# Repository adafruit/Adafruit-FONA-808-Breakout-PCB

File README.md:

## Adafruit FONA 808 Breakout PCB
<a href="http://www.adafruit.com/products/2542"><br/>
Click here to purchase one from the Adafruit shop</a>

Cellular + GPS tracking, all in one? Oh yes! Introducing Adafruit FONA 808 MiniGSM + GPS, an all-in-one cellular phone module with that lets you add location-tracking, voice, text, SMS and data to your project in an adorable little package. (It does not contain a drum machine, tho)

This module measures only 1.75"x1.6" but packs a surprising amount of technology into it's little frame. At the heart is a powerful GSM cellular module (we use the latest SIM808) with integrated GPS. This module can do just about everything.

PCB files for the Adafruit FONA 808 Breakout. The format is EagleCAD schematic and board layout
 https://www.adafruit.com/products/2542 

### License

Adafruit invests time and resources providing this open source design, please support Adafruit and open-source hardware by purchasing products from [Adafruit](https://www.adafruit.com)!

All text above must be included in any redistribution

Designed by Limor Fried/Ladyada for Adafruit Industries.
Creative Commons Attribution/Share-Alike, all text above must be included in any redistribution. 
See license.txt for additional information.

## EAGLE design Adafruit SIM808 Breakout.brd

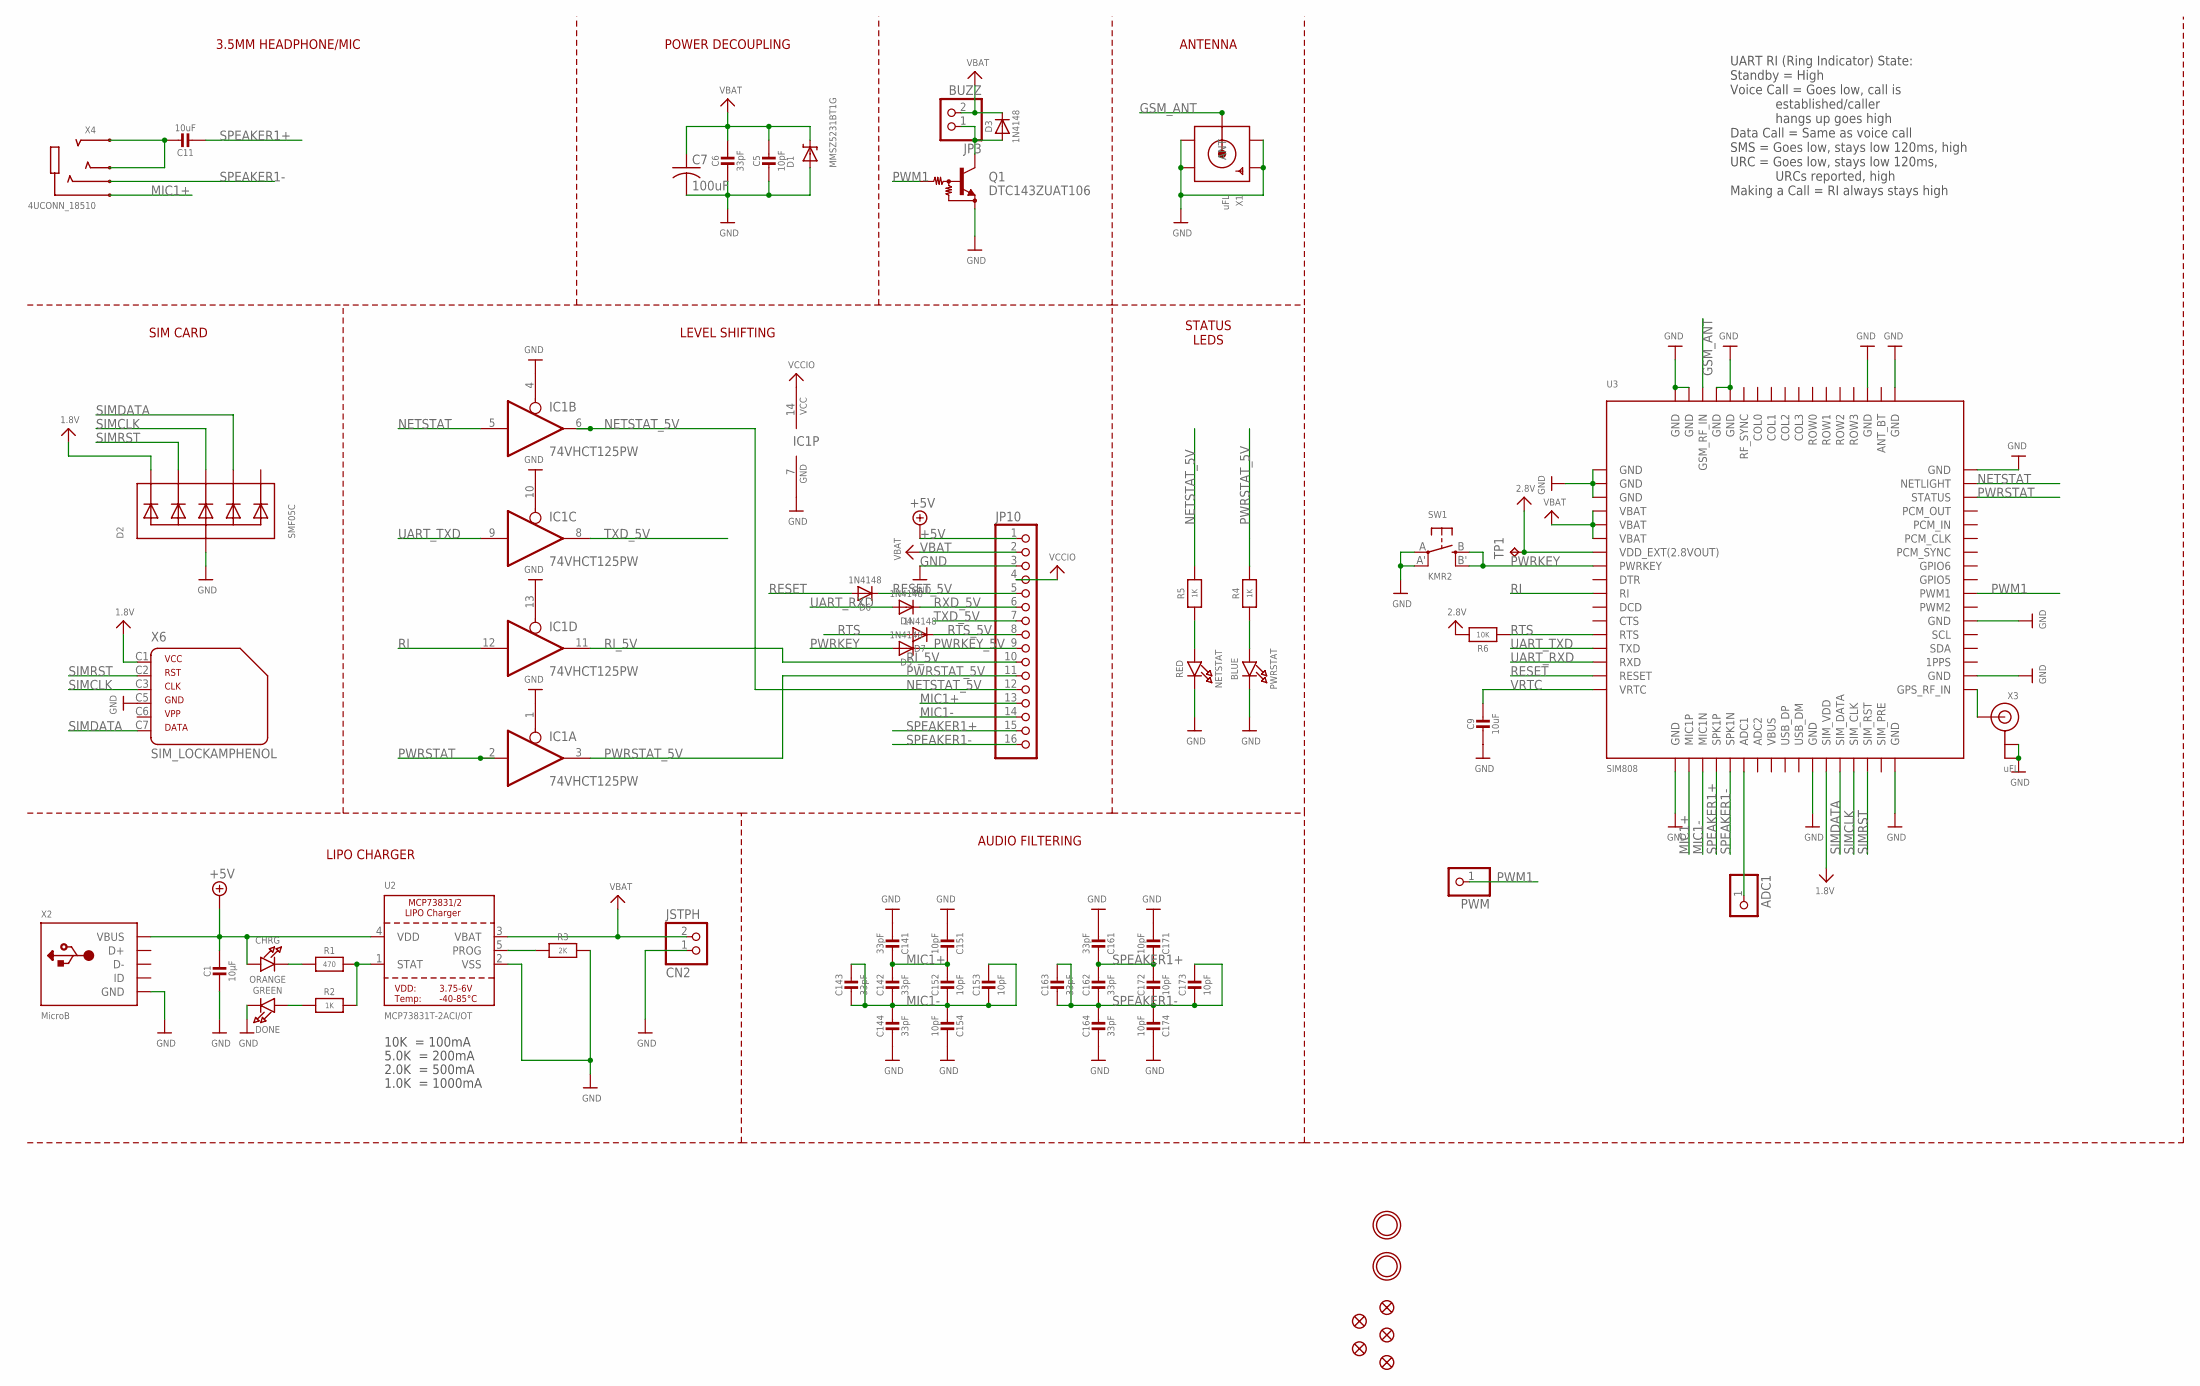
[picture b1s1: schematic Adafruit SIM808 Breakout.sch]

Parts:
ADC1: PINHD-1X1CB; 1X01-CLEANBIG
C1: 10µF; 0805-NO
C5: 10pF; 0805-NO
C6: 33pF; 0805-NO
C7: 100uF; C1210
C9, C11: 10uF; 0805-NO
C14, C16: 33pF; RESPACK_4X0603
C15, C17: 10pF; RESPACK_4X0603
CHRG: ORANGE; CHIPLED_0805_NOOUTLINE
CN2: JSTPH; JSTPH2
D1: MMSZ5231BT1G; SOD-123
D2: SMF05C; SOT363
D3, D4, D5, D6, D7: 1N4148; SOD-323
DONE: GREEN; CHIPLED_0805_NOOUTLINE
FID1, FID2, FID3, FID4, FID5: FIDUCIAL""; FIDUCIAL_1MM
IC1: 74VHCT125PW; TSSOP14
JP3: BUZZ; 1X02_ROUND
JP10: HEADER-1X16ROUND; 1X16_ROUND
NETSTAT: RED; CHIPLED_0805_NOOUTLINE
PWM: PINHD-1X1CB; 1X01-CLEANBIG
PWRSTAT: BLUE; CHIPLED_0805_NOOUTLINE
Q1: DTC143ZUAT106; SC59-BEC
R1: 470; 0805-NO
R2, R4, R5: 1K; 0805-NO
R3: 2K; 0805-NO
R6: 10K; 0805-NO
SW1: KMR2; BTN_KMR2_4.6X2.8
TP1: TPTP11R; TP11R
U2: MCP73831T-2ACI/OT; SOT23-5
U3: SIM808; SIM900_SMT
U$33, U$34: MOUNTINGHOLE2.5; MOUNTINGHOLE_2.5_PLATED
X1: uFL; SMA_EDGELAUNCH_UFL
X2: MicroB; 4UCONN_20329
X3: uFL; U.FL
X4: 4UCONN_18510
X6: SIM_LOCKAMPHENOL; C707_10M006_512_2

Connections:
1.8V: D2.1 (C1), U3.P$29 (SIM_VDD), X6.C1 (1)
2.8V: R6.2, TP1.TP, U3.P$7 (VDD_EXT(2.8VOUT))
+5V: C1.1, CHRG.A, JP10.1, U2.4 (VDD), X2.VBUS
GND: C1.2, C5.2, C6.2, C7.2, C9.2, C14.5 (2), C14.8 (2), C15.4 (1), C15.8 (2), C16.5 (2), C16.8 (2), C17.4 (1), C17.8 (2), CN2.1, D1.A, D2.2 (A), DONE.C, IC1.1 (OE), IC1.4 (OE), IC1.7 (GND), IC1.10 (OE), IC1.13 (OE), JP10.3, NETSTAT.C, PWRSTAT.C, Q1.E, R3.2, SW1.A, SW1.A' (P1), U2.2 (VSS), U3.P$1 (GND), U3.P$2 (GND), U3.P$3 (GND), U3.P$18 (GND), U3.P$28 (GND), U3.P$34 (GND), U3.P$36 (GND), U3.P$40 (GND), U3.P$51 (GND), U3.P$52 (GND), U3.P$54 (GND), U3.P$64 (GND), U3.P$65 (GND), U3.P$67 (GND), U3.P$68 (GND), X1.GND@1 (GND1), X1.GND@2 (GND2), X1.GND@3 (GND3), X1.GND@4 (GND4), X2.BASE@1 (GND), X2.BASE@2 (GND), X2.GND, X2.SPRT@1 (GND), X2.SPRT@2 (GND), X2.SPRT@3 (GND), X2.SPRT@4 (GND), X3.1 (GND), X3.2 (GND), X6.C5 (4)
GSM_ANT: U3.P$66 (GSM_RF_IN), X1.P (ANT)
HP+: C11.1, X4.2-TIP (RING3), X4.3-OUTER_SLEEVE (RING2)
MIC1+: C14.1, C14.2 (1), C15.1, C15.2 (1), JP10.13, U3.P$19 (MIC1P), X4.1-GND (TIP)
MIC1-: C14.3 (1), C14.4 (1), C14.6 (2), C14.7 (2), C15.3 (1), C15.5 (2), C15.6 (2), C15.7 (2), JP10.14, U3.P$20 (MIC1N)
unnamed: CHRG.C, R1.1
unnamed: R1.2, R2.2, U2.1 (STAT)
unnamed: U3.P$35 (GPS_RF_IN), X3.3 (SIGNAL)
unnamed: PWRSTAT.A, R4.1
unnamed: R3.1, U2.5 (PROG)
unnamed: DONE.A, R2.1
unnamed: ADC1.1, U3.P$23 (ADC1)
unnamed: NETSTAT.A, R5.1
unnamed: D3.A, JP3.1, Q1.C
NETSTAT: IC1.5 (I), U3.P$50 (NETLIGHT)
NETSTAT_5V: IC1.6 (O), JP10.12, R5.2
PWM1: PWM.1, Q1.B, U3.P$42 (PWM1)
PWRKEY: D5.A, SW1.B (S), SW1.B' (S1), U3.P$8 (PWRKEY)
PWRKEY_5V: D5.C, JP10.9
PWRSTAT: IC1.2 (I), U3.P$49 (STATUS)
PWRSTAT_5V: IC1.3 (O), JP10.11, R4.2
RESET: D6.A, U3.P$16 (RESET)
RESET_5V: D6.C, JP10.5
RI: IC1.12 (I), U3.P$10 (RI)
RI_5V: IC1.11 (O), JP10.10
RTS: D7.A, R6.1, U3.P$13 (RTS)
RTS_5V: D7.C, JP10.8
RXD_5V: D4.C, JP10.6
SIMCLK: D2.4 (C3), U3.P$31 (SIM_CLK), X6.C3 (3)
SIMDATA: D2.5 (C4), U3.P$30 (SIM_DATA), X6.C7 (6)
SIMRST: D2.3 (C2), U3.P$32 (SIM_RST), X6.C2 (2)
SPEAKER1+: C11.2, C16.1, C16.2 (1), C17.1, C17.2 (1), JP10.15, U3.P$21 (SPK1P)
SPEAKER1-: C16.3 (1), C16.4 (1), C16.6 (2), C16.7 (2), C17.3 (1), C17.5 (2), C17.6 (2), C17.7 (2), JP10.16, U3.P$22 (SPK1N), X4.4-INNER_SLEEVE (RING1)
TXD_5V: IC1.8 (O), JP10.7
UART_RXD: D4.A, U3.P$15 (RXD)
UART_TXD: IC1.9 (I), U3.P$14 (TXD)
VBAT: C5.1, C6.1, C7.1, CN2.2, D1.C, D3.C, JP3.2, JP10.2, U2.3 (VBAT), U3.P$4 (VBAT), U3.P$5 (VBAT), U3.P$6 (VBAT)
VBUS: U3.P$25 (VBUS)
VCCIO: IC1.14 (VCC), JP10.4
VRTC: C9.1, U3.P$17 (VRTC)

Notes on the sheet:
10K = 100mA
5.0K = 200mA
2.0K = 500mA
1.0K = 1000mA
UART RI (Ring Indicator) State: Standby = High Voice Call = Goes low, call is established/caller hangs up goes high Data Call = Same as voice call SMS = Goes low, stays low 120ms, high URC = Goes low, stays low 120ms, URCs reported, high Making a Call = RI always stays high
ANTENNA
POWER DECOUPLING
3.5MM HEADPHONE/MIC
SIM CARD
LEVEL SHIFTING
LIPO CHARGER
AUDIO FILTERING
STATUS LEDS

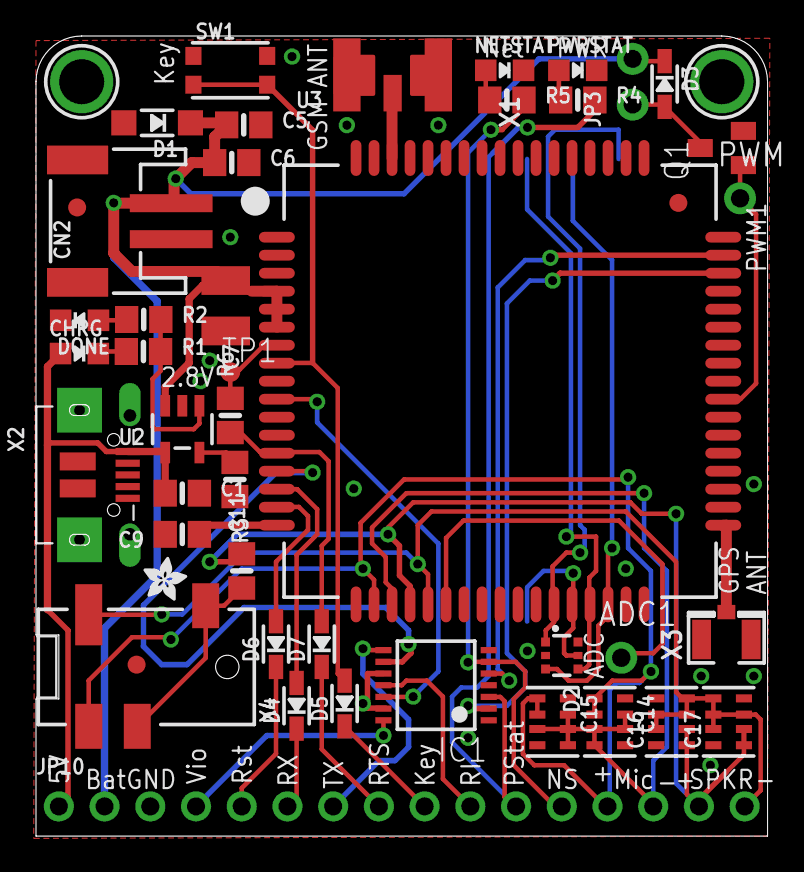
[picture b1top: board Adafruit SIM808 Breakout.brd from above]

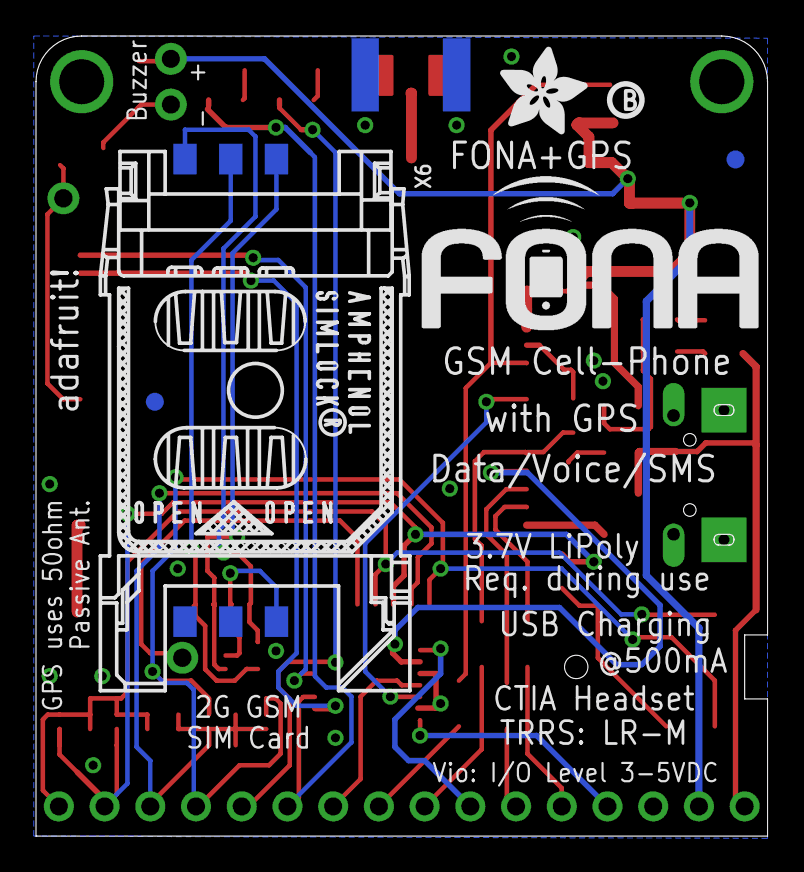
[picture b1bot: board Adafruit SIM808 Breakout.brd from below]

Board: 2 copper layers, 40.6 x 44.5 mm, 54 parts (6 on the bottom side), 42 nets.

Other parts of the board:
U$21: ADAFRUIT_2.5MM
U$25: PCBFEAT-REV-040
U$26: FONA_LOGO
U$36: ADAFRUIT_5MM

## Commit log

2016-05-10 init

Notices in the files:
parts and their libraries:
microbuilder: This work is placed in the public domain, and may be freely used for commercial and non-commercial work with the following conditions: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
